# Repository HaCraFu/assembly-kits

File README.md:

# HaCraFu assembly kits

[Documentation](https://hacrafu.github.io/assembly-kits)

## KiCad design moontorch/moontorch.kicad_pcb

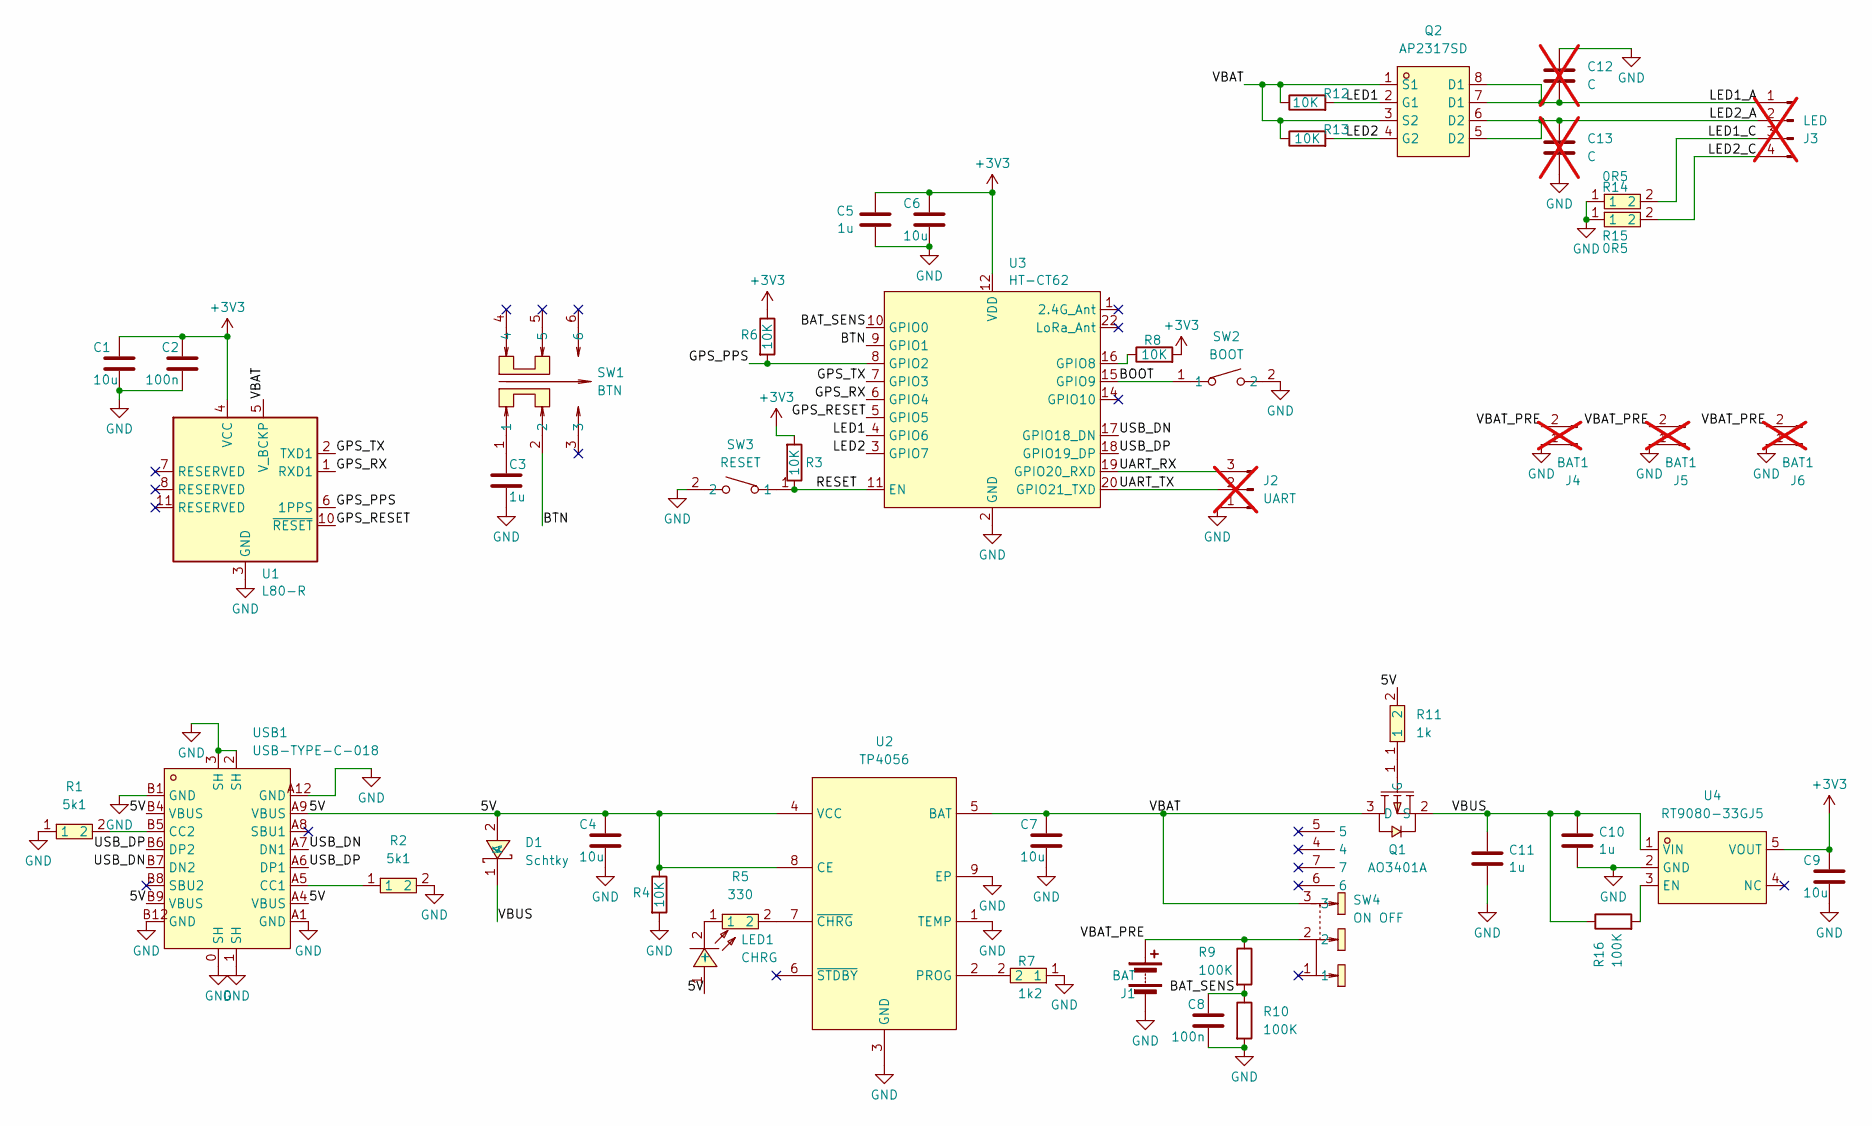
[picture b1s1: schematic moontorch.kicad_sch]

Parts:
C1, C4, C6, C7, C9: 10u; C_0603_1608Metric_Pad1.08x0.95mm_HandSolder; LCSC Part C19702
C2, C8: 100n; C_0603_1608Metric_Pad1.08x0.95mm_HandSolder; LCSC Part C14663
C3, C5, C10, C11: 1u; C_0603_1608Metric_Pad1.08x0.95mm_HandSolder; LCSC Part C15849
C12, C13: C; C_0603_1608Metric_Pad1.08x0.95mm_HandSolder; not fitted
D1: Schtky; SOD-323_L1.8-W1.3-LS2.5-RD; LCSC Part C191023
J1: BAT; Battery 230525
J2: UART; PinHeader_1x03_P2.54mm_Vertical; not fitted
J3: LED; PinHeader_1x04_P2.54mm_Vertical; not fitted
J4, J5, J6: BAT1; PinHeader_1x02_P2.54mm_Vertical; not fitted
LED1: CHRG; LED_0805_2012Metric_Pad1.15x1.40mm_HandSolder; LCSC Part C2296
Q1: AO3401A; SOT-23_L2.9-W1.3-P1.90-LS2.4-BR; LCSC Part C15127
Q2: AP2317SD; SOP-8_L4.9-W3.9-P1.27-LS6.0-BL; LCSC Part C5443692
R1, R2: 5k1; R_0603_1608Metric_Pad0.98x0.95mm_HandSolder; LCSC Part C23186
R3, R4, R6, R8, R12, R13: 10K; R_0603_1608Metric_Pad0.98x0.95mm_HandSolder; LCSC Part C25804
R5: 330; R_0603_1608Metric_Pad0.98x0.95mm_HandSolder; LCSC Part C23138
R7: 1k2; R_0603_1608Metric_Pad0.98x0.95mm_HandSolder; LCSC Part C22765
R9, R10, R16: 100K; R_0603_1608Metric_Pad0.98x0.95mm_HandSolder; LCSC Part C25803
R11: 1k; R_0603_1608Metric_Pad0.98x0.95mm_HandSolder; LCSC Part C21190
R14, R15: 0R5; R_1206_3216Metric_Pad1.30x1.75mm_HandSolder; LCSC Part C25340
SW1: BTN; SW-SMD_6P-L5.8-W5.8-P2.00-LS8.5-TR; LCSC Part C840833
SW2: BOOT; SW-SMD_L3.9-W3.0-P4.45; LCSC Part C720477
SW3: RESET; SW-SMD_L3.9-W3.0-P4.45; LCSC Part C720477
SW4: ON OFF; SW-TH_K3-1296S-E1; LCSC Part C128955
U1: L80-R; Quectel_L80-R
U2: TP4056; ESOP-8_L4.9-W3.9-P1.27-LS6.0-BL-EP; LCSC Part C16581
U3: HT-CT62; Heltec_HT-CT62
U4: RT9080-33GJ5; TSOT-23-5_L2.9-W1.6-P0.95-LS2.8-BL; LCSC Part C841192
USB1: USB-TYPE-C-018; USB-C_SMD-TYPE-C-31-M-12; LCSC Part C2927038

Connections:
+3V3: C1.1, C2.1, C5.1, C6.1, C9.1, R3.2, R6.1, R8.2, U1.4 (VCC), U3.12 (VDD), U4.5 (VOUT)
/5V: C4.1, D1.2 (A), LED1.1 (+), R4.1, R11.2, U2.4 (VCC), U2.8 (CE), USB1.A4 (VBUS), USB1.A9 (VBUS), USB1.B4 (VBUS), USB1.B9 (VBUS)
/BAT_SENS: C8.1, R9.2, R10.1, U3.10 (GPIO0)
/BOOT: SW2.1, U3.15 (GPIO9)
/BTN: SW1.2, U3.9 (GPIO1)
/GPS_PPS: R6.2, U1.6 (1PPS), U3.8 (GPIO2)
/GPS_RESET: U1.10 (~RESET), U3.5 (GPIO5)
/GPS_RX: U1.1 (RXD1), U3.6 (GPIO4)
/GPS_TX: U1.2 (TXD1), U3.7 (GPIO3)
/LED1: Q2.2 (G1), R12.2, U3.4 (GPIO6)
/LED1_A: C12.2, J3.1, Q2.7 (D1), Q2.8 (D1)
/LED1_C: J3.3, R14.2
/LED2: Q2.4 (G2), R13.2, U3.3 (GPIO7)
/LED2_A: C13.1, J3.2, Q2.5 (D2), Q2.6 (D2)
/LED2_C: J3.4, R15.2
/RESET: R3.1, SW3.1, U3.11 (EN)
/UART_RX: J2.3, U3.19 (GPIO20_RXD)
/UART_TX: J2.2, U3.20 (GPIO21_TXD)
/USB_DN: U3.17 (GPIO18_DN), USB1.A7 (DN1), USB1.B7 (DN2)
/USB_DP: U3.18 (GPIO19_DP), USB1.A6 (DP1), USB1.B6 (DP2)
/VBAT: C7.1, Q1.3 (D), Q2.1 (S1), Q2.3 (S2), R12.1, R13.1, SW4.3, U1.5 (V_BCKP), U2.5 (BAT)
/VBAT_PRE: J1.1 (+), J4.2, J5.2, J6.2, R9.1, SW4.2
/VBUS: C10.1, C11.1, D1.1 (K), Q1.2 (S), R16.1, U4.1 (VIN)
GND: C1.2, C2.2, C3.2, C4.2, C5.2, C6.2, C7.2, C8.2, C9.2, C10.2, C11.2, C12.1, C13.2, J1.2 (-), J2.1, J4.1, J5.1, J6.1, R1.1, R2.2, R4.2, R7.1, R10.2, R14.1, R15.1, SW2.2, SW3.2, U1.3 (GND), U1.12 (GND), U2.1 (TEMP), U2.3 (GND), U2.9 (EP), U3.2 (GND), U3.13 (GND), U3.21 (GND), U4.2 (GND), USB1.0 (SH), USB1.1 (SH), USB1.2 (SH), USB1.3 (SH), USB1.A1 (GND), USB1.A12 (GND), USB1.B1 (GND), USB1.B12 (GND)
unnamed: C3.1, SW1.1
unnamed: LED1.2 (-), R5.1
unnamed: Q1.1 (G), R11.1
unnamed: R7.2, U2.2 (PROG)
unnamed: R5.2, U2.7 (~CHRG)
unnamed: R8.1, U3.16 (GPIO8)
unnamed: R16.2, U4.3 (EN)
unnamed: R2.1, USB1.A5 (CC1)
unnamed: R1.2, USB1.B5 (CC2)

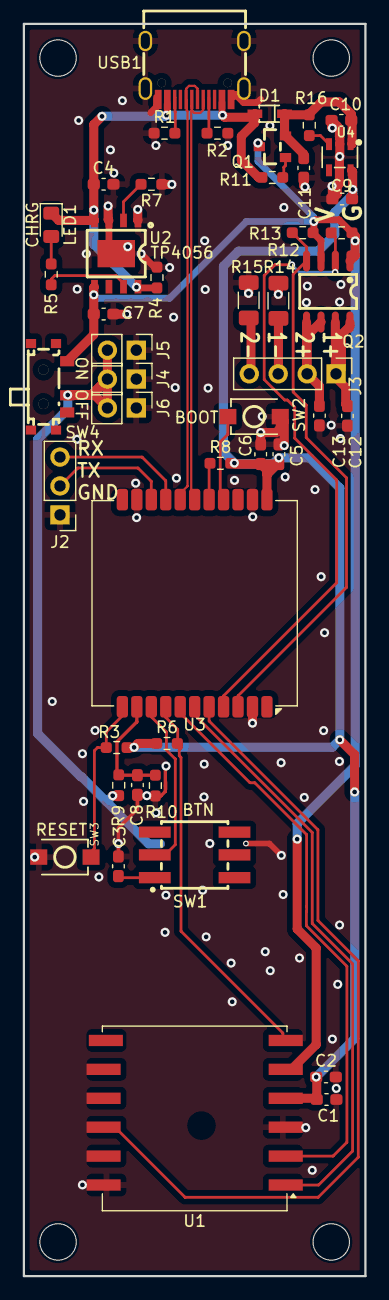
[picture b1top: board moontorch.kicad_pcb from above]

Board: 2 copper layers, 30.0 x 110.0 mm, 48 parts (1 on the bottom side), 33 nets.

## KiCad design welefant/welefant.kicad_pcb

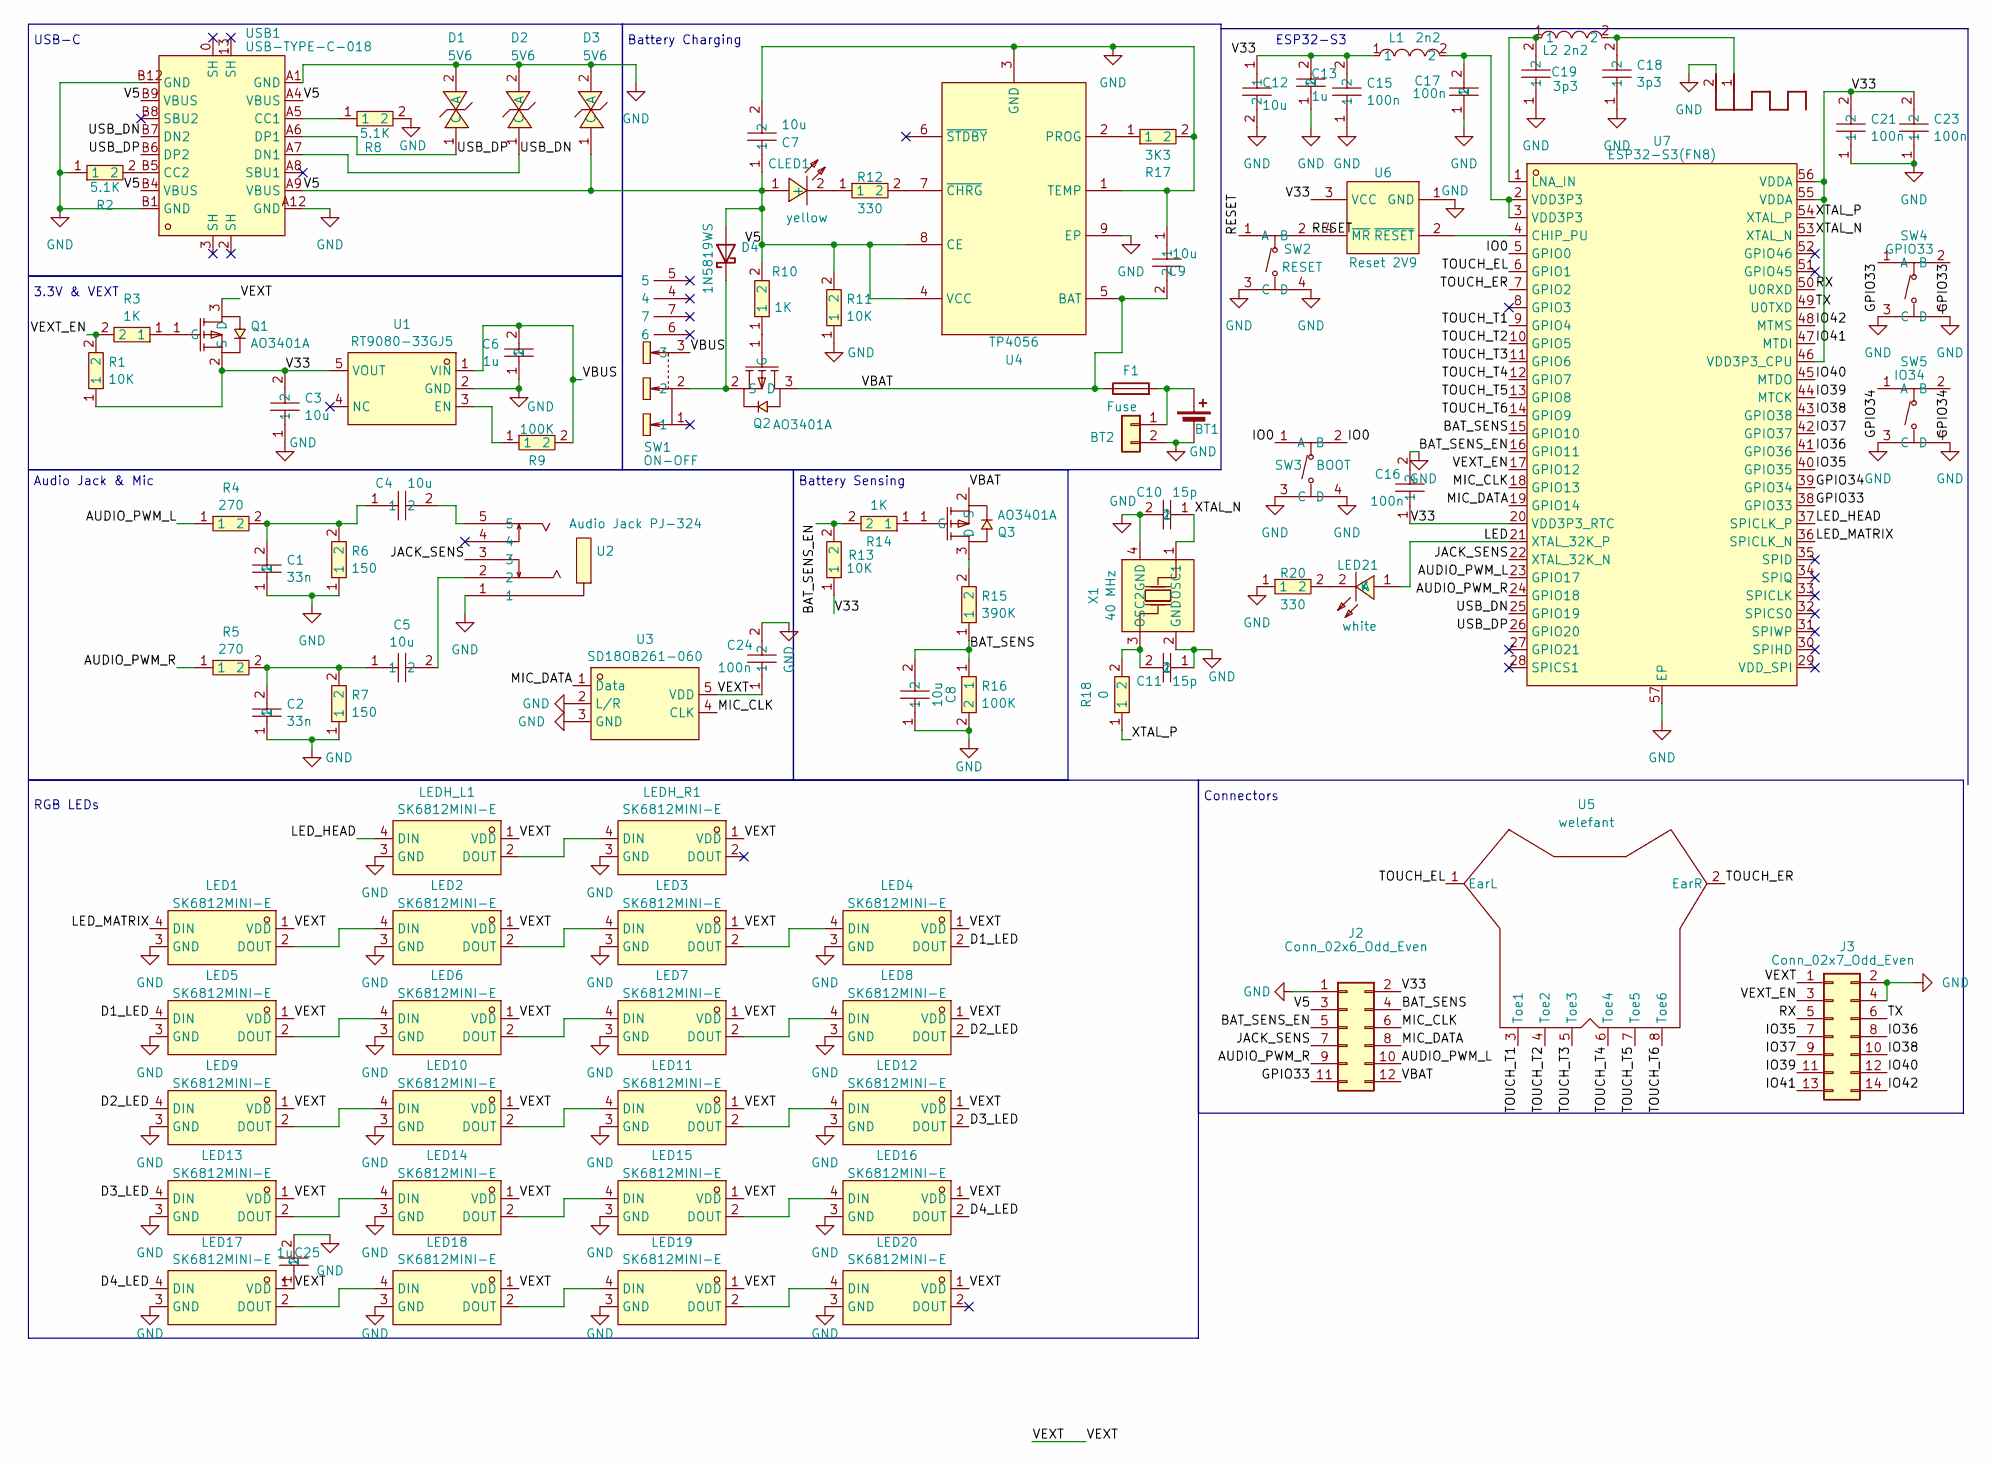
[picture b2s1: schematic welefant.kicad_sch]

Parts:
ANT1: ANTENNA; antenna
BT1: Battery; LiPo_Recycled_welefant
BT2: Conn_01x02; JST_XH_B2B-XH-A_1x02_P2.50mm_Vertical
C1, C2: 33n; C0603; LCSC Part C21117
C3, C4, C5, C7, C8, C9, C12: 10u; C0603; LCSC Part C19702
C6, C13, C25: 1u; C0603; LCSC Part C15849
C10, C11: 15p; C0603; LCSC Part C1644
C15, C16, C21, C23, C24: 100n; C0603; LCSC Part C14663
C17: 100n; C0402_NEW; LCSC Part C1525
C18, C19: 3p3; C0603; LCSC Part C162224
CLED1: yellow; LED0805-R-RD; LCSC Part C2296
D1, D2, D3: 5V6; SOD-882_L1.0-W0.6-BI; LCSC Part C7420372
D4: 1N5819WS; D_SOD-323; LCSC Part C191023
F1: Fuse; F0805; LCSC Part C914095
J2: Conn_02x6_Odd_Even; PinHeader_2x06_P2.54mm_Vertical_SMD_handsolder
J3: Conn_02x7_Odd_Even; PinHeader_2x07_P2.54mm_Vertical_SMD_handsolder
L1, L2: 2n2; L0603; LCSC Part C29682
LED1, LED2, LED3, LED4, LED5, LED6, LED7, LED8, LED9, LED10, LED11, LED12, LED13, LED14, LED15, LED16, LED17, LED18, LED19, LED20: SK6812MINI-E; SK6812MINI-E-handsolder; LCSC Part C5149201
LED21: white; LED0603-R-RD_WHITE; LCSC Part C2290
LEDH_L1: SK6812MINI-E; SK6812MINI-E-handsolder; LCSC Part C5149201
LEDH_R1: SK6812MINI-E; SK6812MINI-E-handsolder; LCSC Part C5149201
Q1, Q2, Q3: AO3401A; SOT-23_L2.9-W1.3-P1.90-LS2.4-BR; LCSC Part C15127
R1, R11, R13: 10K; R0603; LCSC Part C25804
R2, R8: 5.1K; R0603; LCSC Part C23186
R3, R10, R14: 1K; R0603; LCSC Part C21190
R4, R5: 270; R0603; LCSC Part C22966
R6, R7: 150; R0603; LCSC Part C22808
R9, R16: 100K; R0603; LCSC Part C25803
R12, R20: 330; R0603; LCSC Part C23138
R15: 390K; R0603; LCSC Part C23150
R17: 3K3; R0603_NEW; LCSC Part C22978
R18: 0; R0603; LCSC Part C21189
SW1: ON-OFF; SW-TH_K3-1296S-E1; LCSC Part C128955
SW2: RESET; SW-SMD_4P-L5.1-W5.1-P3.70-LS6.5-TL-2; LCSC Part C318884
SW3: BOOT; SW-SMD_4P-L5.1-W5.1-P3.70-LS6.5-TL-2; LCSC Part C318884
SW4: GPIO33; SW-SMD_4P-L5.1-W5.1-P3.70-LS6.5-TL-2; LCSC Part C318884
SW5: IO34; SW-SMD_4P-L5.1-W5.1-P3.70-LS6.5-TL-2; LCSC Part C318884
U1: RT9080-33GJ5; TSOT-23-5_L2.9-W1.6-P0.95-LS2.8-BL; LCSC Part C841192
U2: Audio Jack PJ-324; AUDIO-TH_PJ-32400; LCSC Part C2884956
U3: SD18OB261-060; MIC-SMD_SD18OB261-060; LCSC Part C2895290
U4: TP4056; ESOP-8_L4.9-W3.9-P1.27-LS6.0-BL-EP; LCSC Part C16581
U5: welefant
U6: Reset 2V9; SOT-143_L2.9-W1.3-P1.92-LS2.3-BR; LCSC Part C42421911
U7: ESP32-S3(FN8); QFN-56_L7.0-W7.0-P0.40-TL-EP4.0; LCSC Part C2913196
USB1: USB-TYPE-C-018; USB-C_SMD-TYPE-C-31-M-12; LCSC Part C2927038
X1: 40 MHz; OSC-SMD_4P-L3.2-W2.5-BL_SIT8008BI; LCSC Part C9010

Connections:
/AUDIO_PWM_L: J2.10, R4.1, U7.23 (GPIO17)
/AUDIO_PWM_R: J2.9, R5.1, U7.24 (GPIO18)
/BAT_SENS: C8.2, J2.4, R15.1, R16.1, U7.15 (GPIO10)
/BAT_SENS_EN: J2.5, R13.2, R14.2, U7.16 (GPIO11)
/D1_LED: LED4.2 (DOUT), LED5.4 (DIN)
/D2_LED: LED8.2 (DOUT), LED9.4 (DIN)
/D3_LED: LED12.2 (DOUT), LED13.4 (DIN)
/D4_LED: LED16.2 (DOUT), LED17.4 (DIN)
/GPIO33: J2.11, SW4.1 (A), SW4.2 (B), U7.38 (GPIO33)
/GPIO34: SW5.1 (A), SW5.2 (B), U7.39 (GPIO34)
/IO0: SW3.1 (A), SW3.2 (B), U7.5 (GPIO0)
/IO35: J3.7, U7.40 (GPIO35)
/IO36: J3.8, U7.41 (GPIO36)
/IO37: J3.9, U7.42 (GPIO37)
/IO38: J3.10, U7.43 (GPIO38)
/IO39: J3.11, U7.44 (MTCK)
/IO40: J3.12, U7.45 (MTDO)
/IO41: J3.13, U7.47 (MTDI)
/IO42: J3.14, U7.48 (MTMS)
/JACK_SENS: J2.7, U2.3, U7.22 (XTAL_32K_N)
/LED: LED21.1 (A), U7.21 (XTAL_32K_P)
/LED_HEAD: LEDH_L1.4 (DIN), U7.37 (SPICLK_P)
/LED_MATRIX: LED1.4 (DIN), U7.36 (SPICLK_N)
/MIC_CLK: J2.6, U3.4 (CLK), U7.18 (GPIO13)
/MIC_DATA: J2.8, U3.1 (Data), U7.19 (GPIO14)
/RESET: SW2.1 (A), SW2.2 (B), U6.4 (~MR)
/RX: J3.5, U7.50 (U0RXD)
/TOUCH_EL: U5.1 (EarL), U7.6 (GPIO1)
/TOUCH_ER: U5.2 (EarR), U7.7 (GPIO2)
/TOUCH_T1: U5.3 (Toe1), U7.9 (GPIO4)
/TOUCH_T2: U5.4 (Toe2), U7.10 (GPIO5)
/TOUCH_T3: U5.5 (Toe3), U7.11 (GPIO6)
/TOUCH_T4: U5.6 (Toe4), U7.12 (GPIO7)
/TOUCH_T5: U5.7 (Toe5), U7.13 (GPIO8)
/TOUCH_T6: U5.8 (Toe6), U7.14 (GPIO9)
/TX: J3.6, U7.49 (U0TXD)
/USB_DN: D2.1 (C), U7.25 (GPIO19), USB1.A7 (DN1), USB1.B7 (DN2)
/USB_DP: D1.1 (C), U7.26 (GPIO20), USB1.A6 (DP1), USB1.B6 (DP2)
/V5: C7.1, CLED1.1 (+), D3.1 (C), D4.2 (A), J2.3, R10.2, R11.2, U4.4 (VCC), U4.8 (CE), USB1.A4 (VBUS), USB1.A9 (VBUS), USB1.B4 (VBUS), USB1.B9 (VBUS)
/V33: C3.2, C12.1, C13.2, C15.2, C16.1, C21.2, C23.2, J2.2, L1.1, Q1.2 (S), R1.1, R13.1, U1.5 (VOUT), U6.3 (VCC), U7.20 (VDD3P3_RTC), U7.46 (VDD3P3_CPU), U7.55 (VDDA), U7.56 (VDDA)
/VBAT: C9.2, F1.1, J2.12, Q2.3 (D), Q3.2 (S), U4.5 (BAT)
/VBUS: C6.2, R9.2, SW1.3, U1.1 (VIN)
/VEXT: C24.1, C25.1, J3.1, LED1.1 (VDD), LED2.1 (VDD), LED3.1 (VDD), LED4.1 (VDD), LED5.1 (VDD), LED6.1 (VDD), LED7.1 (VDD), LED8.1 (VDD), LED9.1 (VDD), LED10.1 (VDD), LED11.1 (VDD), LED12.1 (VDD), LED13.1 (VDD), LED14.1 (VDD), LED15.1 (VDD), LED16.1 (VDD), LED17.1 (VDD), LED18.1 (VDD), LED19.1 (VDD), LED20.1 (VDD), LEDH_L1.1 (VDD), LEDH_R1.1 (VDD), Q1.3 (D), U3.5 (VDD)
/VEXT_EN: J3.3, R1.2, R3.2, U7.17 (GPIO12)
/XTAL_N: C10.1, U7.53 (XTAL_N), X1.1 (OSC1)
/XTAL_P: R18.1, U7.54 (XTAL_P)
GND: ANT1.2 (GND), BT1.2 (-), BT2.2, C1.1, C2.1, C3.1, C6.1, C7.2, C8.1, C9.1, C10.2, C11.1, C12.2, C13.1, C15.1, C16.2, C17.1, C18.1, C19.1, C21.1, C23.1, C24.2, C25.2, D1.2 (A), D2.2 (A), D3.2 (A), J2.1, J3.2, J3.4, LED1.3 (GND), LED2.3 (GND), LED3.3 (GND), LED4.3 (GND), LED5.3 (GND), LED6.3 (GND), LED7.3 (GND), LED8.3 (GND), LED9.3 (GND), LED10.3 (GND), LED11.3 (GND), LED12.3 (GND), LED13.3 (GND), LED14.3 (GND), LED15.3 (GND), LED16.3 (GND), LED17.3 (GND), LED18.3 (GND), LED19.3 (GND), LED20.3 (GND), LEDH_L1.3 (GND), LEDH_R1.3 (GND), R2.1, R6.1, R7.1, R8.2, R11.1, R16.2, R17.2, R20.1, SW2.3 (C), SW2.4 (D), SW3.3 (C), SW3.4 (D), SW4.3 (C), SW4.4 (D), SW5.3 (C), SW5.4 (D), U1.2 (GND), U2.1, U3.2 (L/R), U3.3 (GND), U4.1 (TEMP), U4.3 (GND), U4.9 (EP), U6.1 (GND), U7.57 (EP), USB1.A1 (GND), USB1.A12 (GND), USB1.B1 (GND), USB1.B12 (GND), X1.2 (GND), X1.4 (GND)
unnamed: ANT1.1 (FEED), C18.2, L2.2
unnamed: BT1.1 (+), BT2.1, F1.2
unnamed: C1.2, C4.1, R4.2, R6.2
unnamed: C2.2, C5.1, R5.2, R7.2
unnamed: C4.2, U2.5
unnamed: C5.2, U2.2
unnamed: C17.2, L1.2, U7.2 (VDD3P3), U7.3 (VDD3P3)
unnamed: CLED1.2 (-), R12.1
unnamed: D4.1 (K), Q2.2 (S), SW1.2
unnamed: LED1.2 (DOUT), LED2.4 (DIN)
unnamed: LED2.2 (DOUT), LED3.4 (DIN)
unnamed: LED3.2 (DOUT), LED4.4 (DIN)
unnamed: LED5.2 (DOUT), LED6.4 (DIN)
unnamed: LED6.2 (DOUT), LED7.4 (DIN)
unnamed: LED7.2 (DOUT), LED8.4 (DIN)
unnamed: LED9.2 (DOUT), LED10.4 (DIN)
unnamed: LED10.2 (DOUT), LED11.4 (DIN)
unnamed: LED11.2 (DOUT), LED12.4 (DIN)
unnamed: LED13.2 (DOUT), LED14.4 (DIN)
unnamed: LED14.2 (DOUT), LED15.4 (DIN)
unnamed: LED15.2 (DOUT), LED16.4 (DIN)
unnamed: LED17.2 (DOUT), LED18.4 (DIN)
unnamed: LED18.2 (DOUT), LED19.4 (DIN)
unnamed: LED19.2 (DOUT), LED20.4 (DIN)
unnamed: LED21.2 (K), R20.2
unnamed: LEDH_L1.2 (DOUT), LEDH_R1.4 (DIN)
unnamed: Q1.1 (G), R3.1
unnamed: Q2.1 (G), R10.1
unnamed: Q3.3 (D), R15.2
unnamed: Q3.1 (G), R14.1
unnamed: R9.1, U1.3 (EN)
unnamed: R17.1, U4.2 (PROG)
unnamed: R12.2, U4.7 (~CHRG)
unnamed: U6.2 (~RESET), U7.4 (CHIP_PU)
unnamed: C19.2, L2.1, U7.1 (LNA_IN)
unnamed: R8.1, USB1.A5 (CC1)
unnamed: R2.2, USB1.B5 (CC2)
unnamed: C11.2, R18.2, X1.3 (OSC2)

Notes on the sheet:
RGB LEDs
Battery Charging
Battery Sensing
Audio Jack & Mic
ESP32-S3
Connectors
USB-C
3.3V & VEXT

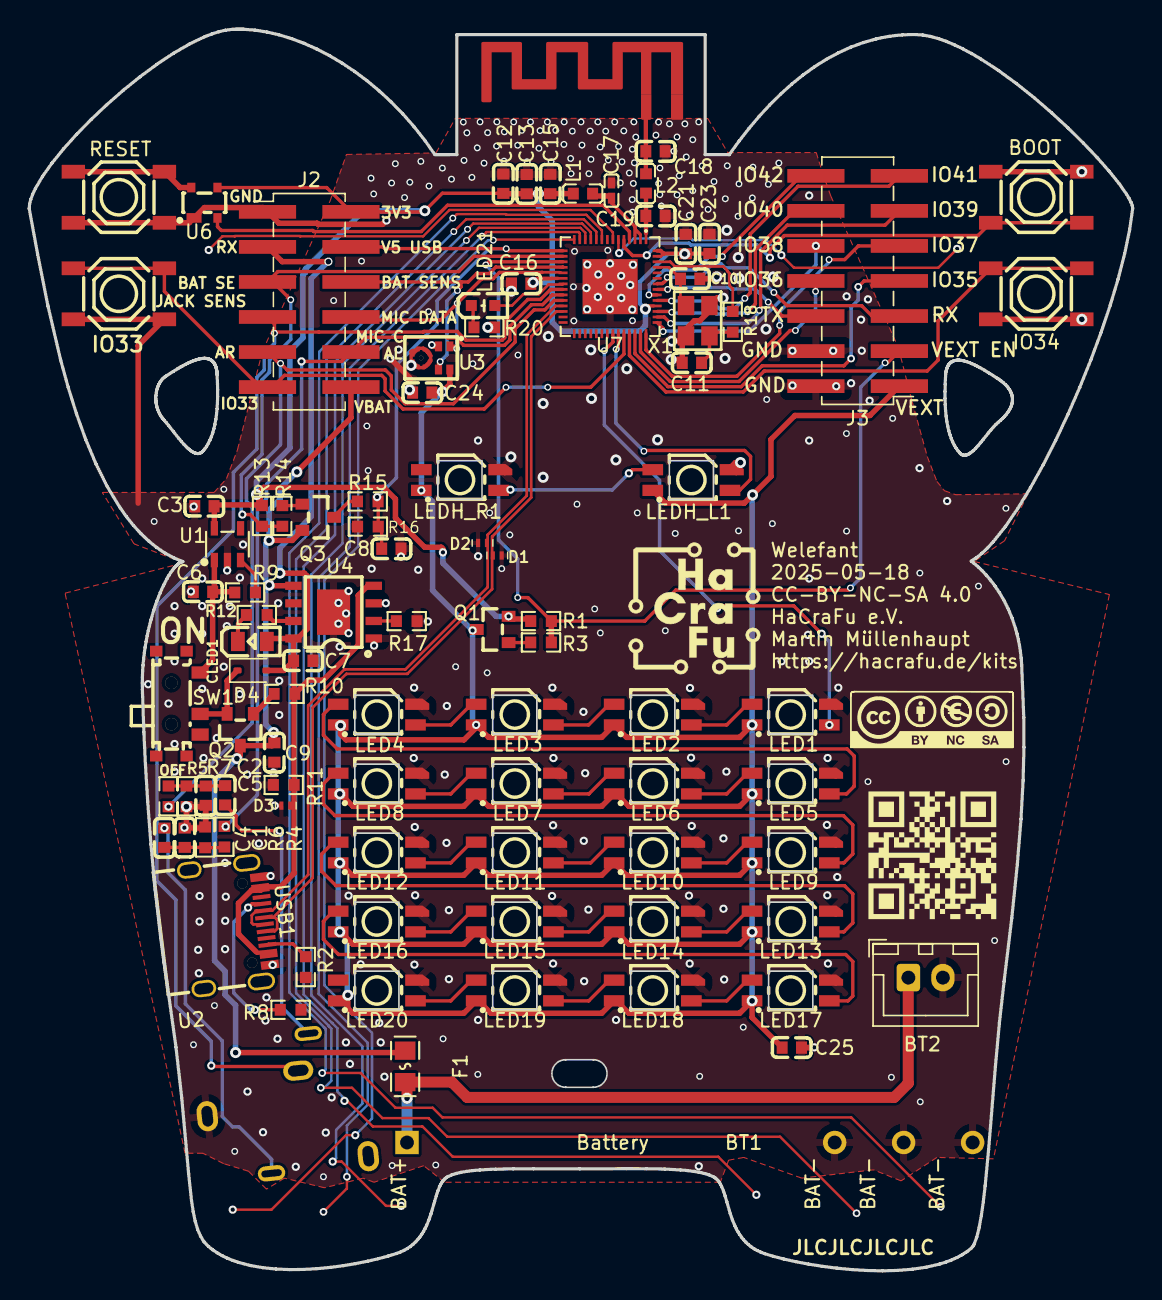
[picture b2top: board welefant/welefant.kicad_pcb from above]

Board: 2 copper layers, 80.0 x 90.0 mm, 94 parts (1 on the bottom side), 85 nets.

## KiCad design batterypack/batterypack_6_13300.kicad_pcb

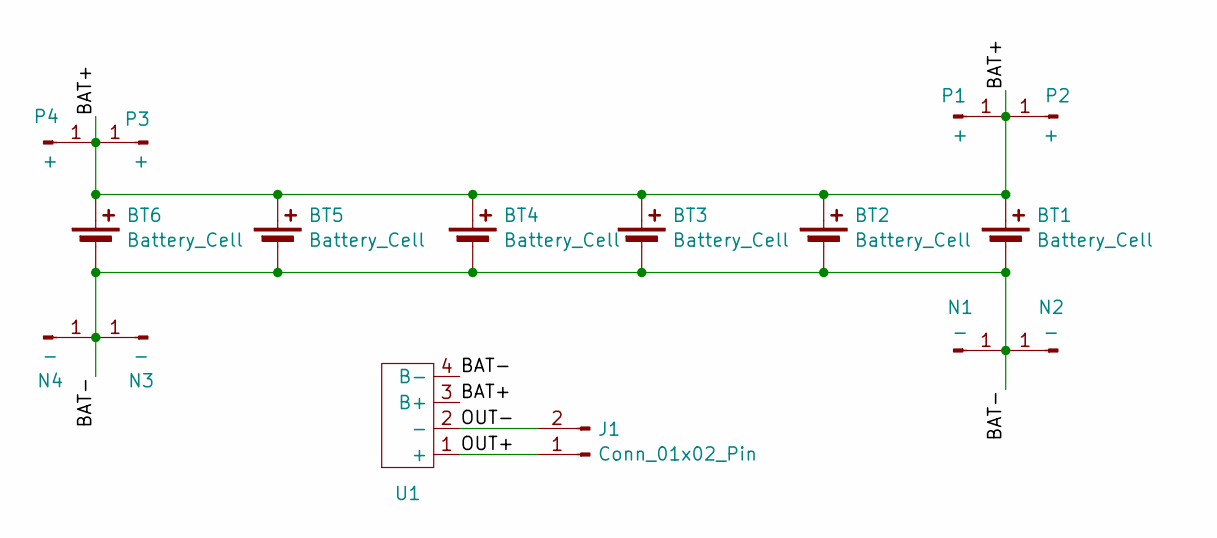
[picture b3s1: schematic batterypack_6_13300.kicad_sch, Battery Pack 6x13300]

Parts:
BT1, BT2, BT3, BT4, BT5, BT6: Battery_Cell; LiPo_Recycled_Array
J1: Conn_01x02_Pin; JST_XH_B2B-XH-AM_1x02_P2.50mm_Vertical
N1, N2, N3, N4: -; SolderWire-2.5sqmm_1x01_D2.4mm_OD4.4mm
P1, P2, P3, P4: +; SolderWire-2.5sqmm_1x01_D2.4mm_OD4.4mm
U1: boost_converter_module

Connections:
/BAT+: BT1.1 (+), BT2.1 (+), BT3.1 (+), BT4.1 (+), BT5.1 (+), BT6.1 (+), P1.1, P2.1, P3.1, P4.1, U1.3 (B+)
/BAT-: BT1.2 (-), BT2.2 (-), BT3.2 (-), BT4.2 (-), BT5.2 (-), BT6.2 (-), N1.1, N2.1, N3.1, N4.1, U1.4 (B-)
/OUT+: J1.1, U1.1 (+)
/OUT-: J1.2, U1.2 (-)

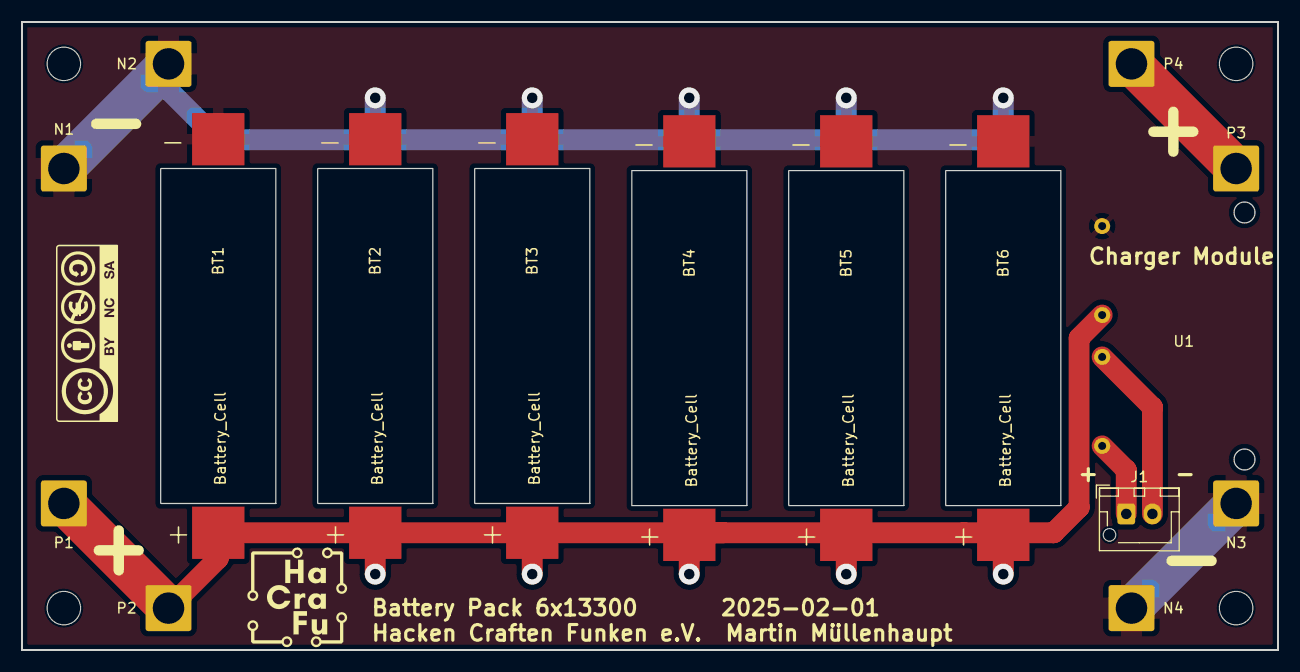
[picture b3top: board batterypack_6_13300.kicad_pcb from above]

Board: 2 copper layers, 120.0 x 60.0 mm, 16 parts (0 on the bottom side), 4 nets.

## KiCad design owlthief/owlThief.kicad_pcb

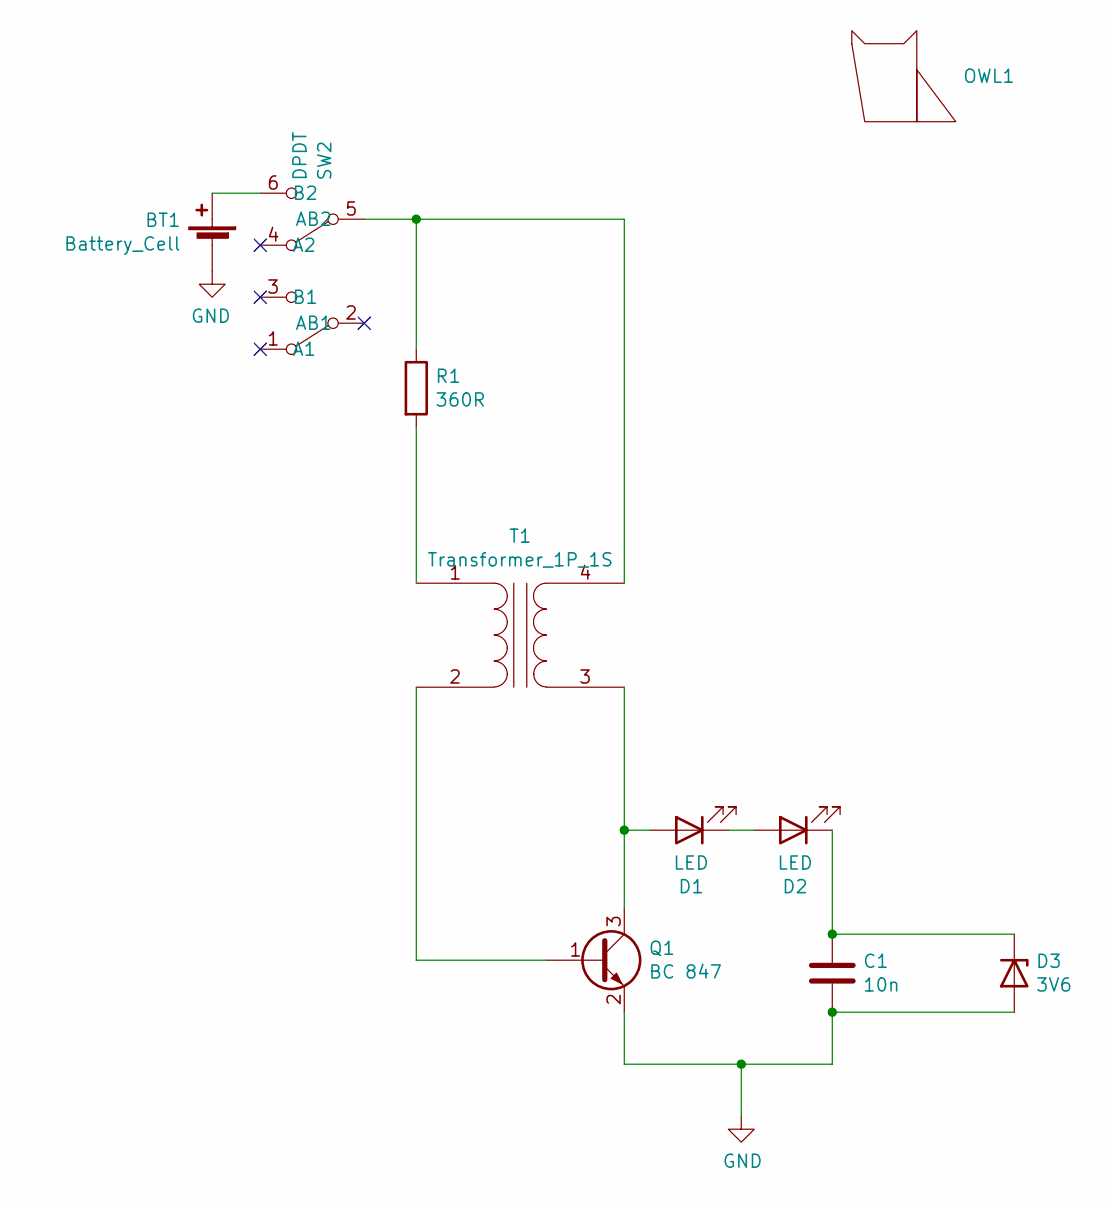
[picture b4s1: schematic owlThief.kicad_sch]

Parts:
BT1: Battery_Cell; Batteryholder AA SMD 1024
C1: 10n; C_1206_3216Metric_Pad1.33x1.80mm_HandSolder
D1, D2: LED; 5mm_SMD-Pad
D3: 3V6; Z-Diode Minimelf
OWL1: owl
Q1: BC 847; SOT-23W_Handsoldering
R1: 360R; R_1206_3216Metric_Pad1.30x1.75mm_HandSolder
SW2: DPDT; Switch_MSS22D18
T1: Transformer_1P_1S; SolderWire-0.1sqmm_1x04_P3.6mm_D0.4mm_OD1mm_SMD

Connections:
GND: BT1.2 (-), C1.2, D3.2 (A), Q1.2 (E)
unnamed: BT1.1 (+), SW2.6 (B2)
unnamed: D1.2 (A), Q1.3 (C), T1.3 (SA)
unnamed: D1.1 (K), D2.2 (A)
unnamed: C1.1, D2.1 (K), D3.1 (K)
unnamed: Q1.1 (B), T1.2 (AB)
unnamed: R1.1, SW2.5 (AB2), T1.4 (SB)
unnamed: R1.2, T1.1 (AA)

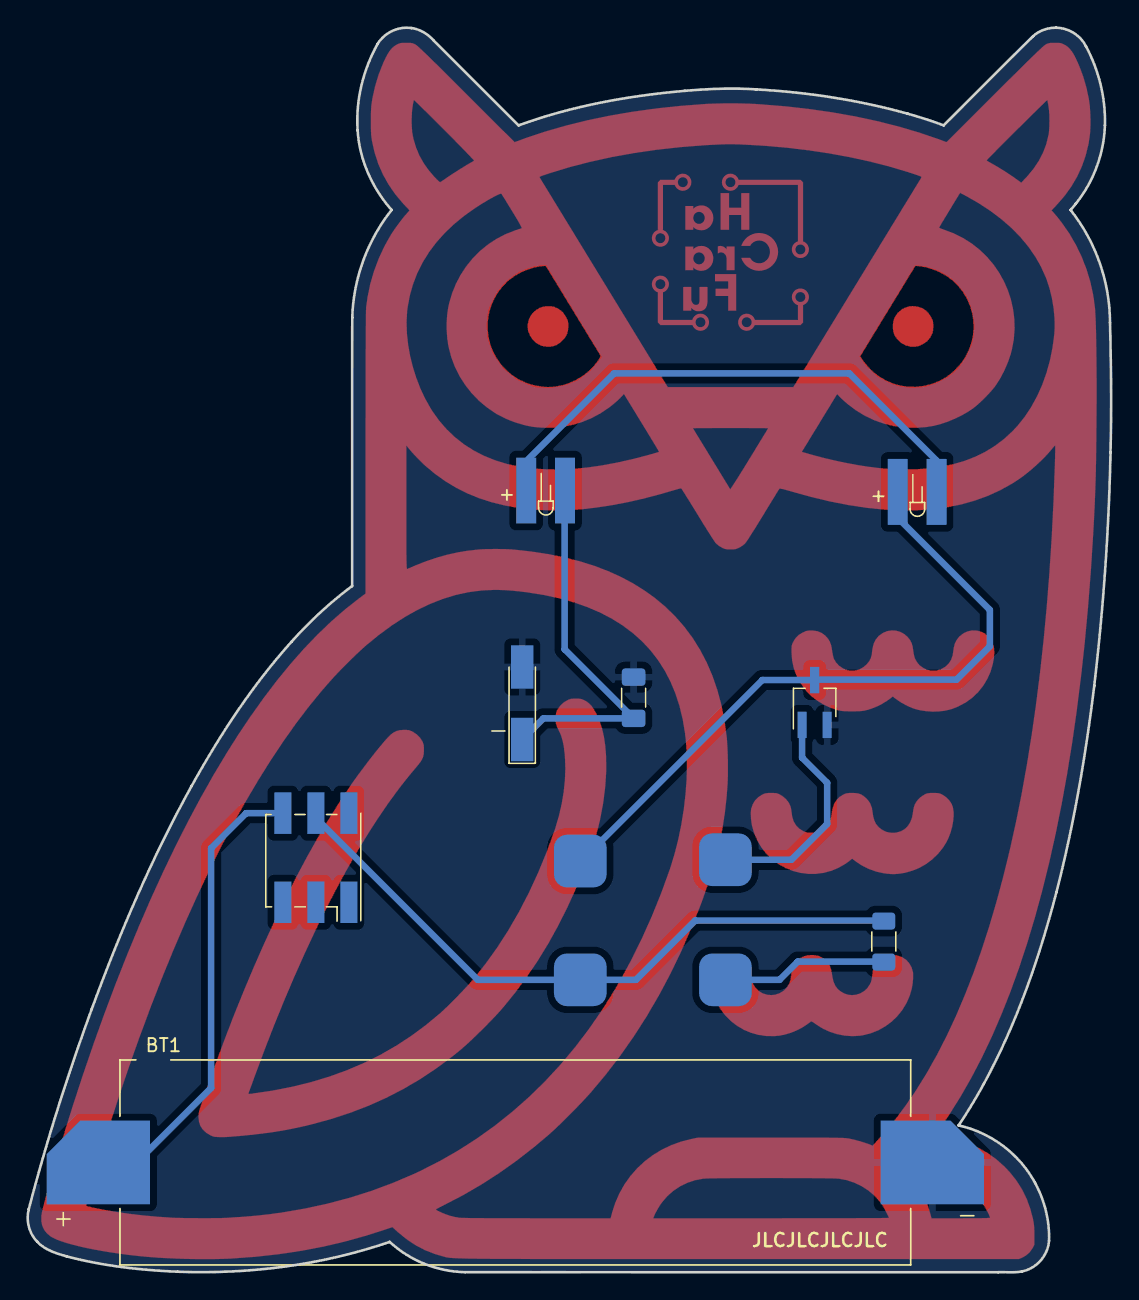
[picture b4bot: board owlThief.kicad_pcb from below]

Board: 2 copper layers, 82.1 x 94.3 mm, 10 parts (9 on the bottom side), 8 nets.

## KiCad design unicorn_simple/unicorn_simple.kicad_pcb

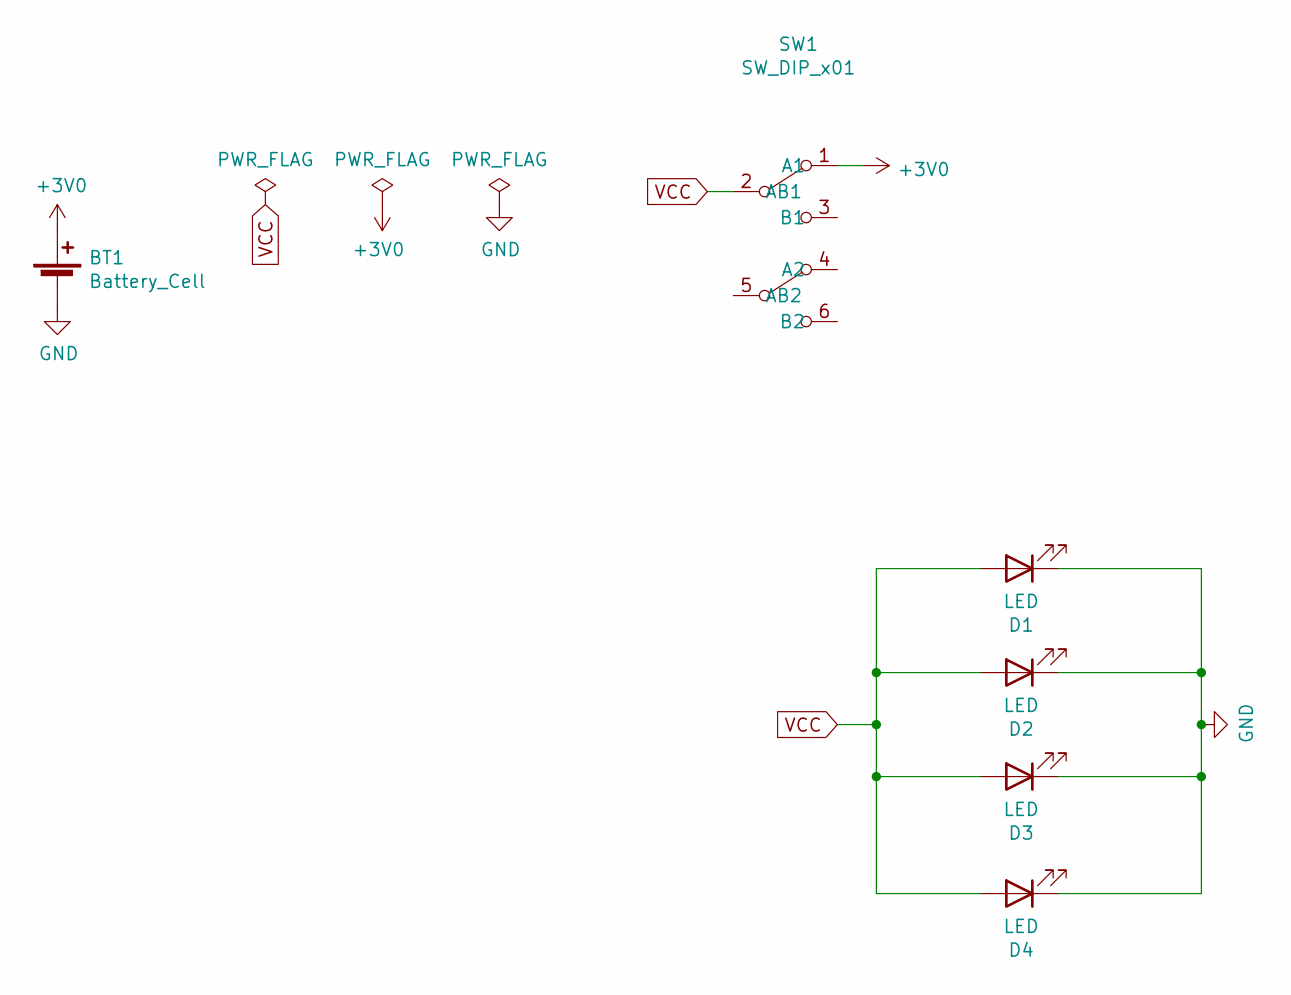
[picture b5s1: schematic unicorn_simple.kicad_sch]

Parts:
BT1: Battery_Cell; Batteryholder
D1, D2, D3, D4: LED; 5mm_SMD-Pad
SW1: SW_DIP_x01; Switch_MSS22D18

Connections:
+3V0: BT1.1 (+), SW1.1 (A1)
GND: BT1.2 (-), D1.1 (K), D2.1 (K), D3.1 (K), D4.1 (K)
VCC: D1.2 (A), D2.2 (A), D3.2 (A), D4.2 (A), SW1.2 (AB1)

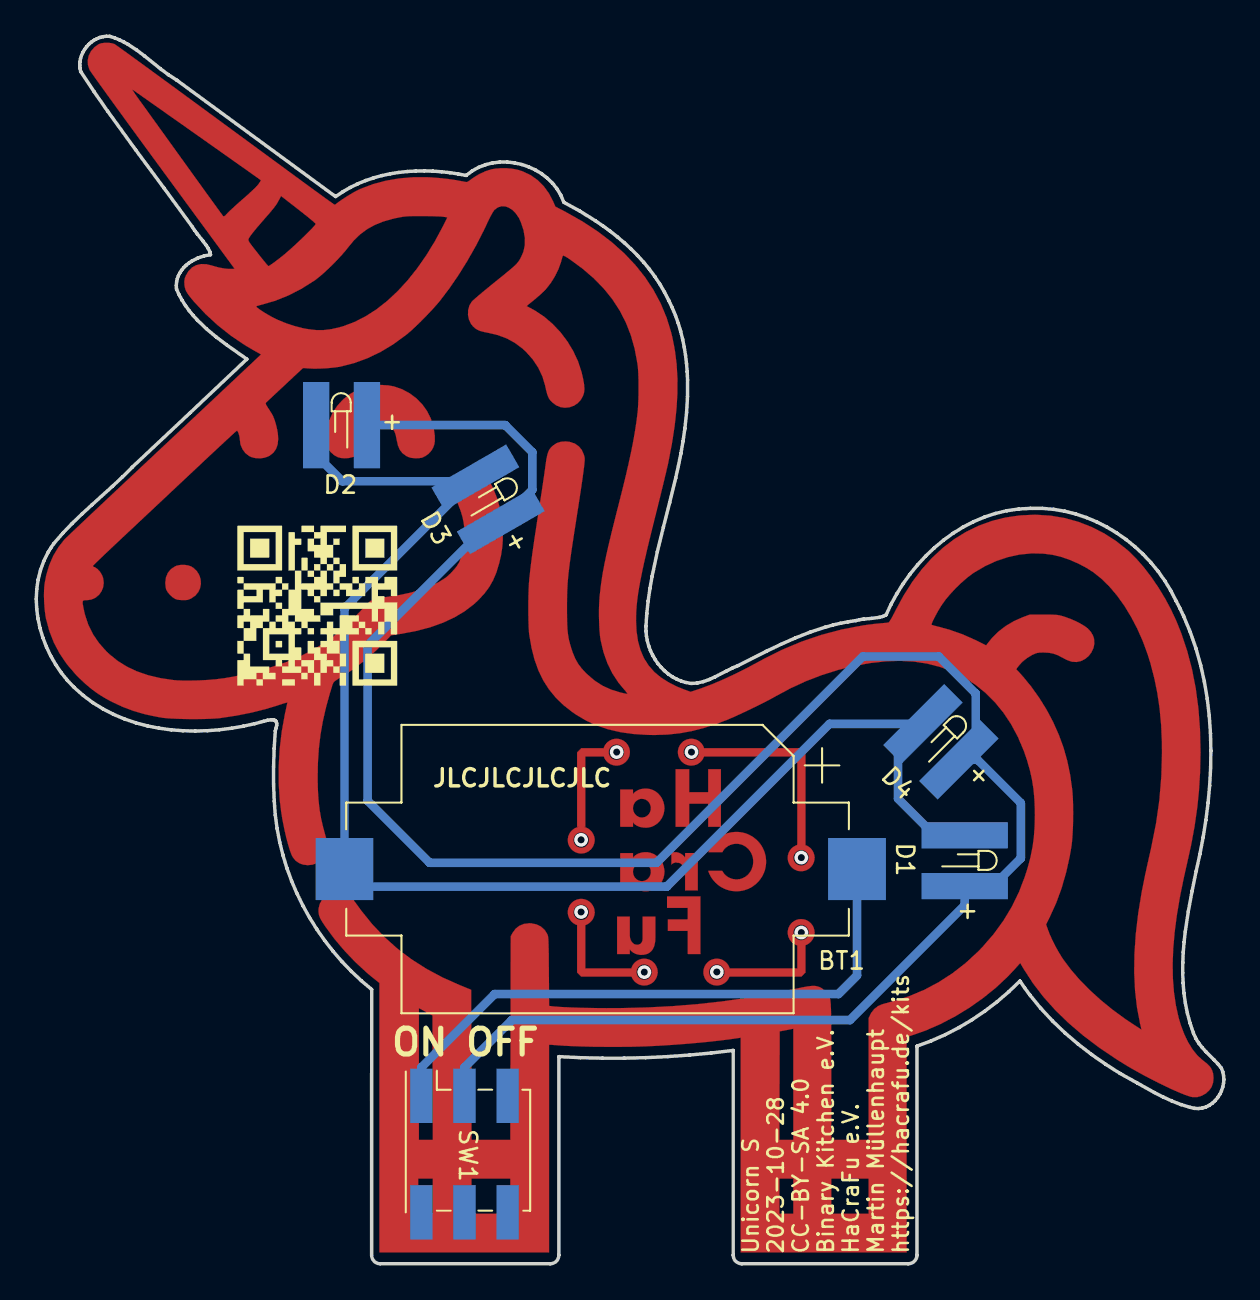
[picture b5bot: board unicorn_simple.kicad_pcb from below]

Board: 2 copper layers, 68.8 x 71.1 mm, 7 parts (6 on the bottom side), 3 nets.

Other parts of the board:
Ref**: Val**; unicorn_simple

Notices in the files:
baumsatz/baumsatz.kicad_pcb:
CC BY-NC-SA 4.0
owlthief/owlThief.kicad_pcb:
CC-BY-SA 4.0
